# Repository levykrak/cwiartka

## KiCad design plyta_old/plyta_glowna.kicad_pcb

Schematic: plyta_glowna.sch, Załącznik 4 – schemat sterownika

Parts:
C1: 220uF
C2, C6, C7, C8: 100nF
C3, C4: 27pF
C9: 100uF
C10, C11, C12, C13: 10uF
D1: zasilnie
D2, D3, D4, D5, D6, D7, D9, D10, D13, D15: DIODE
FB1: 10uH
IC1: ATMEGA8-MI-sterowanie; MLF32
J2: DB9
J3, J4: RJ45-TRANSFO
K1, K2, K3, K4, K5: PRZEKAZNIK1
P1: +12V
P2: ISP_sterowanie
P4: LCD 2x16
P5: CONN_6
P6: Ledy_kontrolne
Q1, Q2, Q3, Q4, Q5: BC337 lub BC548
R1, R9, R10, R12, R13, R15, R16, R17, R19, R20, R21, R23, R24: 470
R2: 10k
R3: 10
R4, R5, R6, R8: 4,7k
R7: 4,7
R11, R14, R18, R22: 100
RV1: 10k
SW1: Start
SW2: KJS
U1: LM7805
U2, U6: SN75176_lewa
U3, U7: SN75176_prawa
U4: MAX232
U5: LM7805_wyswietlacz
X1: 16MHz

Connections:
1: IC1.9 ((T1)PD5), R8.1
2: IC1.10 ((AIN0)PD6), R7.1
3: IC1.11 ((AIN1)PD7), R6.1
4: IC1.12 ((ICP)PB0), R5.1
5: IC1.13 ((OC1A)PB1), R4.1
+5P: P4.15, U5.VO
+5V: C8.2, C9.1, C12.2, D1.1 (A), FB1.1, IC1.4 (VCC), IC1.6 (VCC), P2.2, P4.2, P6.5, R2.1, R10.2, R12.2, R17.2, R20.2, RV1.1, U1.VO, U2.8 (VCC), U3.8 (VCC), U4.16 (VCC), U6.8 (VCC), U7.8 (VCC)
+12V: D2.1 (A), D3.2 (K), D4.2 (K), D5.2 (K), D6.2 (K), D7.2 (K), J3.1 (TD+), J4.1 (TD+), K1.1, K1.5, K2.1, K2.5, K3.1, K3.5, K4.1, K4.5, K5.1, K5.5, P1.2 (PM)
GND: C1.2, C2.1, C3.2, C4.2, C6.2, C7.2, C8.1, C9.2, C13.1, IC1.3 (GND), IC1.5 (GND), IC1.21 (AGND), J2.5, J3.8, J3.13 (SHIELD), J4.8, J4.13 (SHIELD), P1.1, P2.4, P2.6, P2.8, P2.10, P4.1, P4.5, P4.7, P4.8, P4.9, P4.10, P5.6, Q1.E, Q2.E, Q3.E, Q4.E, Q5.E, R1.2, R3.1, R9.2, R13.2, R16.2, R21.2, RV1.3, SW1.2, SW2.2, U1.GND, U2.2 (RE), U2.3 (DE), U2.4 (DI), U2.5 (GND), U3.2 (RE), U3.3 (DE), U3.4 (DI), U3.5 (GND), U4.15 (GND), U5.GND, U6.2 (RE), U6.3 (DE), U6.4 (DI), U6.5 (GND), U7.2 (RE), U7.3 (DE), U7.4 (DI), U7.5 (GND)
unnamed: J4.3 (TD-), R10.1, R11.2, U2.6 (A)
unnamed: D15.1 (A), R24.2, U3.1 (RO)
unnamed: Q1.B, R4.2
unnamed: D3.1 (A), K1.2, Q1.C
unnamed: IC1.22 (ADC7), SW2.1
unnamed: C11.1, U4.4 (C2+)
unnamed: C11.2, U4.5 (C2-)
unnamed: C10.1, U4.1 (C1+)
unnamed: C10.2, U4.3 (C1-)
unnamed: C12.1, U4.2 (V+)
unnamed: J2.3, U4.13 (R1IN)
unnamed: J2.4, J2.6
unnamed: J2.7, J2.8
unnamed: C13.2, U4.6 (V-)
unnamed: K4.4, P5.2
unnamed: K1.4, P5.5
unnamed: K5.4, P5.1
unnamed: J4.4 (RD+), R9.1, R11.1, U2.7 (B)
unnamed: Q4.B, R7.2
unnamed: D6.1 (A), K4.2, Q4.C
unnamed: K2.4, P5.4
unnamed: Q2.B, R5.2
unnamed: D4.1 (A), K2.2, Q2.C
unnamed: D7.1 (A), K5.2, Q5.C
unnamed: Q5.B, R8.2
unnamed: K3.4, P5.3
unnamed: D5.1 (A), K3.2, Q3.C
unnamed: Q3.B, R6.2
unnamed: IC1.23 ((ADC0)PC0), P4.4
unnamed: IC1.24 ((ADC1)PC1), P4.6
unnamed: IC1.15 ((MOSI/OC2)PB3), P2.1
unnamed: IC1.16 ((MISO)PB4), P2.9
unnamed: IC1.17 ((SCK)PB5), P2.7
unnamed: IC1.19 (ADC6), SW1.1
unnamed: C3.1, IC1.7 (PB6(XTAL1/TOSC1)), X1.1
unnamed: IC1.31 ((TXD)PD1), U4.11 (T1IN)
unnamed: IC1.25 ((ADC2)PC2), P4.11
unnamed: IC1.27 ((ADC4/SDA)PC4), P4.13
unnamed: IC1.30 ((RXD)PD0), U4.12 (R1OUT)
unnamed: P4.3, RV1.2
unnamed: IC1.26 ((ADC3)PC3), P4.12
unnamed: IC1.28 ((ADC5/SCL)PC5), P4.14
unnamed: P4.16, R3.2
unnamed: J2.2, U4.14 (T1OUT)
unnamed: C1.1, C2.2, D2.2 (K), U1.VI, U5.VI
unnamed: C4.1, IC1.8 (PB7(XTAL2/TOSC2)), X1.2
unnamed: C6.1, IC1.20 (AREF)
unnamed: D1.2 (K), R1.1
unnamed: C7.1, FB1.2, IC1.18 (AVCC)
unnamed: IC1.29 (PC6(~RESET~)), P2.5, R2.2
unnamed: J4.5 (RCT), R12.1, R14.1, U3.6 (A)
unnamed: D10.2 (K), D15.2 (K), IC1.1 ((INT1)PD3)
unnamed: J4.6 (RD-), R13.1, R14.2, U3.7 (B)
unnamed: D9.1 (A), R15.2, U6.1 (RO)
unnamed: D9.2 (K), D13.2 (K), IC1.32 ((INT0)PD2)
unnamed: D13.1 (A), R23.2, U2.1 (RO)
unnamed: J3.5 (RCT), R20.1, R22.1, U7.6 (A)
unnamed: J3.4 (RD+), R16.1, R18.1, U6.7 (B)
unnamed: J3.6 (RD-), R21.1, R22.2, U7.7 (B)
unnamed: D10.1 (A), R19.2, U7.1 (RO)
unnamed: J3.3 (TD-), R17.1, R18.2, U6.6 (A)
lewa_meta: P6.3, R15.1
lewa_start: P6.1, R23.1
prawa_meta: P6.4, R19.1
prawa_start: P6.2, R24.1

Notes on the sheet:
ISP
Zasilanie
Wyswietlacz

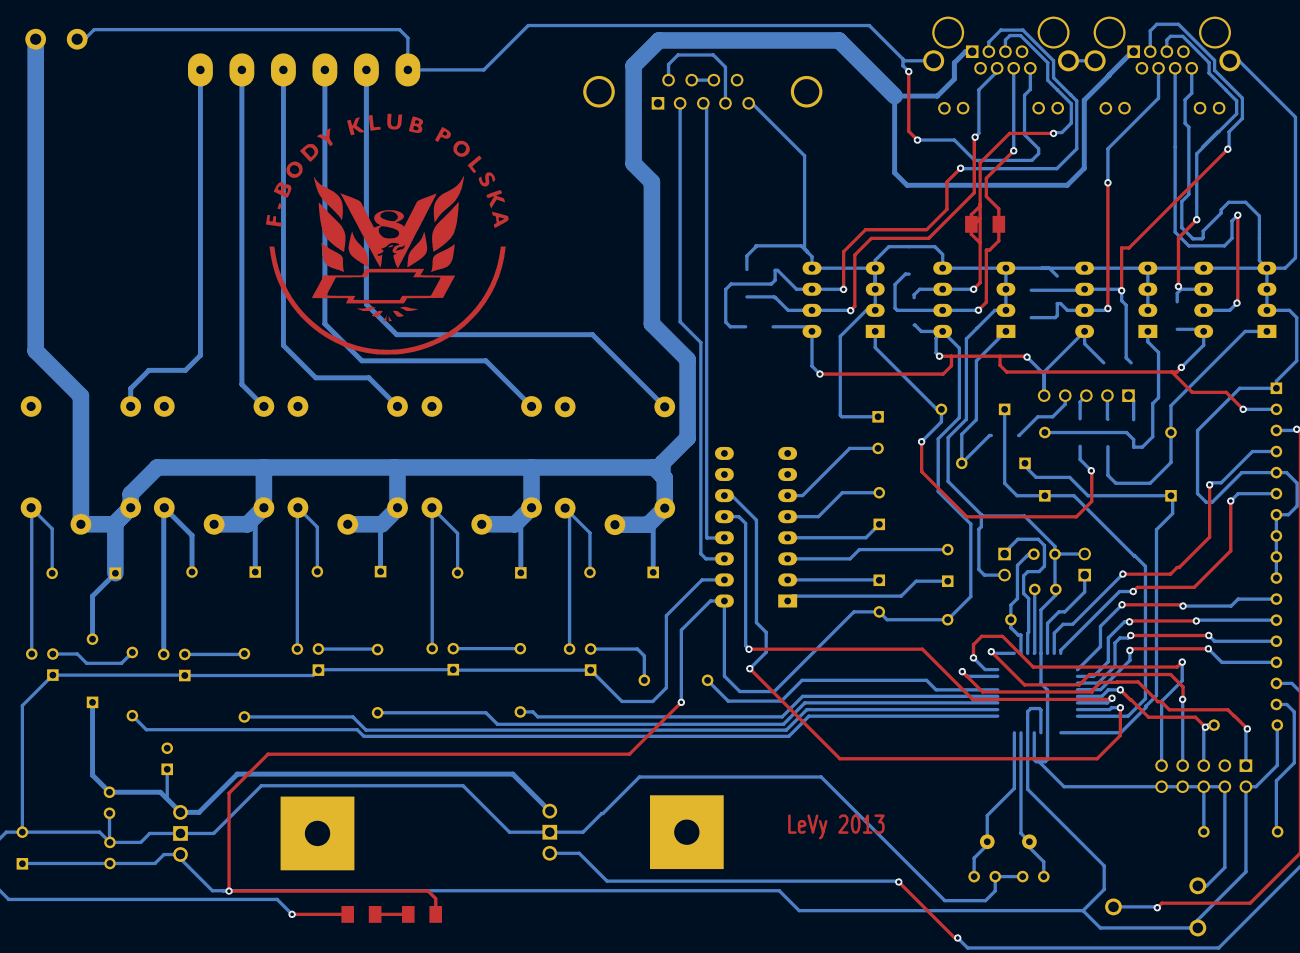
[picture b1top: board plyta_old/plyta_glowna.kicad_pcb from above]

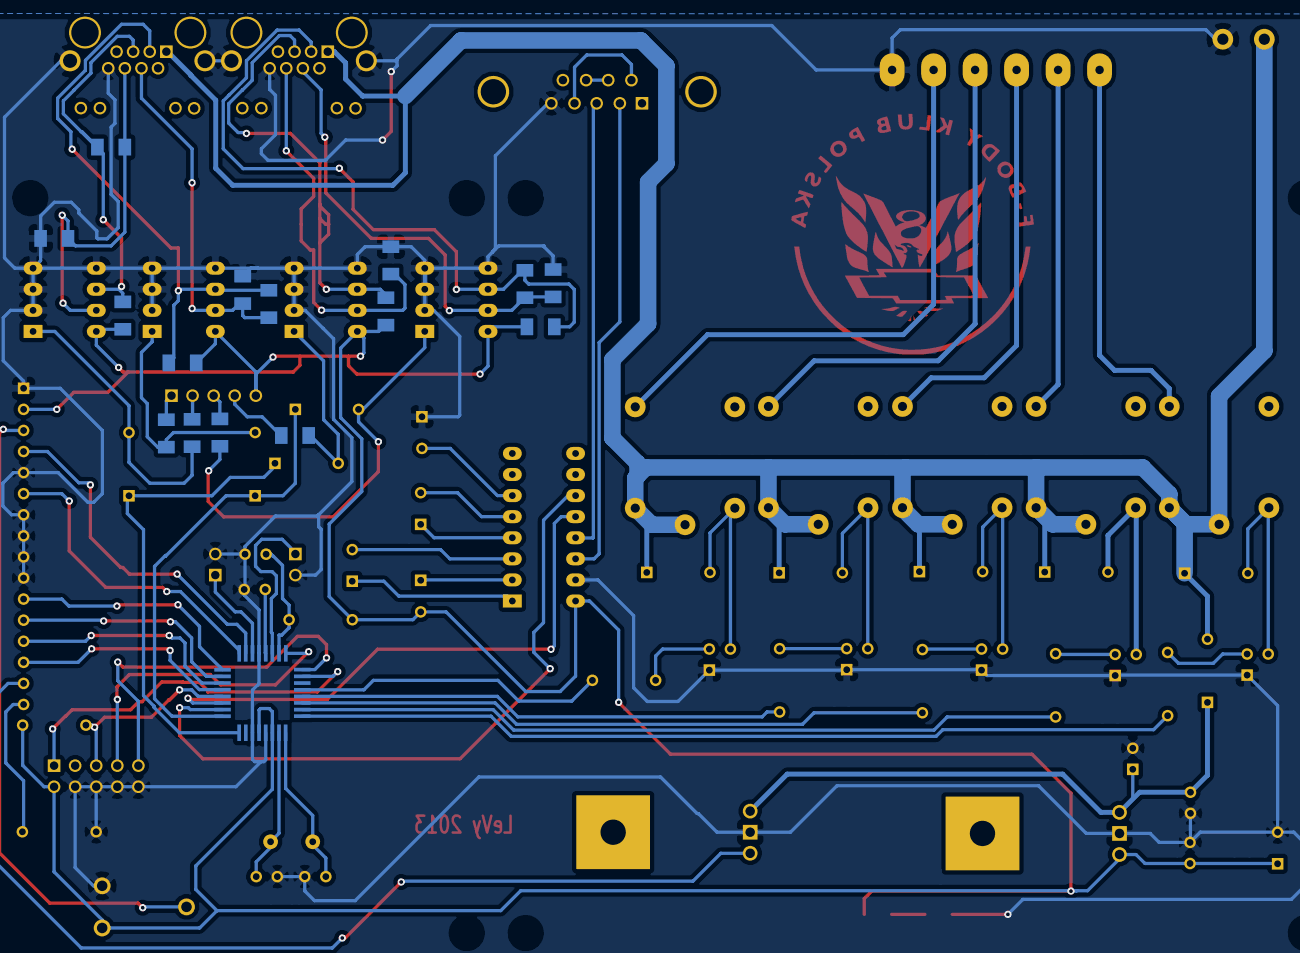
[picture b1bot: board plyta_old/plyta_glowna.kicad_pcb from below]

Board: 2 copper layers, 79 parts (16 on the bottom side), 74 nets.

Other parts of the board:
VAL: logo_fbody_plyta

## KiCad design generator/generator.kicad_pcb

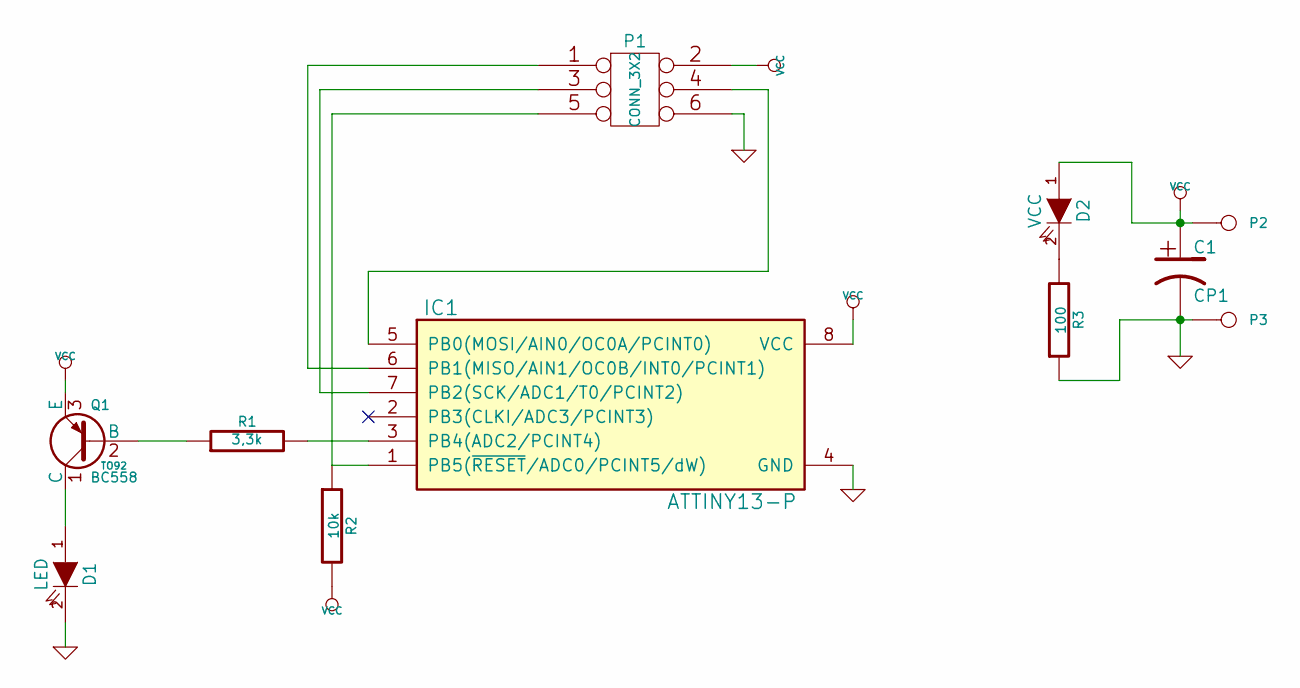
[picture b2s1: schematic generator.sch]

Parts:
C1: CP1
D1: LED
D2: VCC
IC1: ATTINY13-P; DIP8
P1: CONN_3X2
P2, P3: CONN_1
Q1: BC558; TO92
R1: 3,3k
R2: 10k
R3: 100

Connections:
GND: C1.2, D1.2 (K), IC1.4 (GND), P1.6, P3.1, R3.1
unnamed: IC1.1 (PB5(~RESET~/ADC0/PCINT5/dW)), P1.5, R2.1
unnamed: D1.1 (A), Q1.1 (C)
unnamed: IC1.3 (PB4(ADC2/PCINT4)), R1.2
unnamed: Q1.2 (B), R1.1
unnamed: IC1.5 (PB0(MOSI/AIN0/OC0A/PCINT0)), P1.4
unnamed: D2.2 (K), R3.2
unnamed: IC1.7 (PB2(SCK/ADC1/T0/PCINT2)), P1.3
unnamed: IC1.6 (PB1(MISO/AIN1/OC0B/INT0/PCINT1)), P1.1
VCC: C1.1, D2.1 (A), IC1.8 (VCC), P1.2, P2.1, Q1.3 (E), R2.2

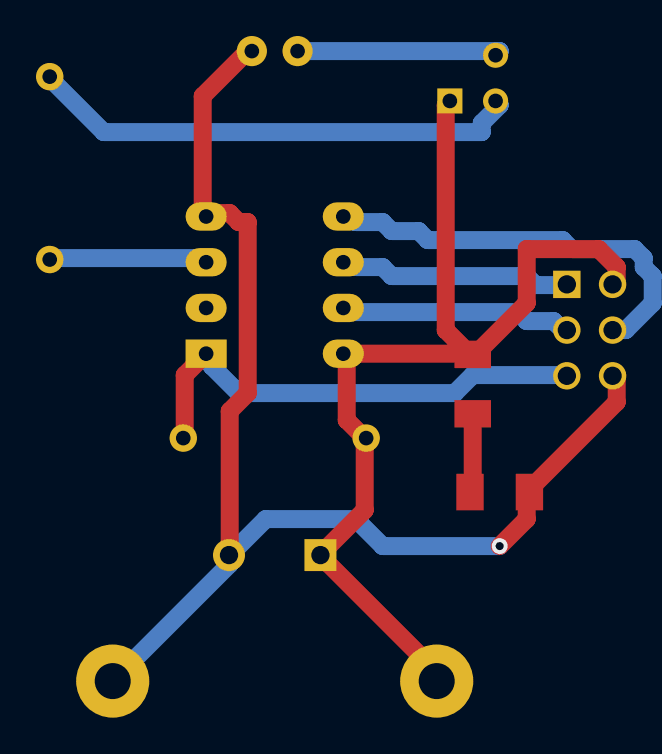
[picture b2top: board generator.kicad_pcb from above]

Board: 2 copper layers, 11 parts (0 on the bottom side), 10 nets.

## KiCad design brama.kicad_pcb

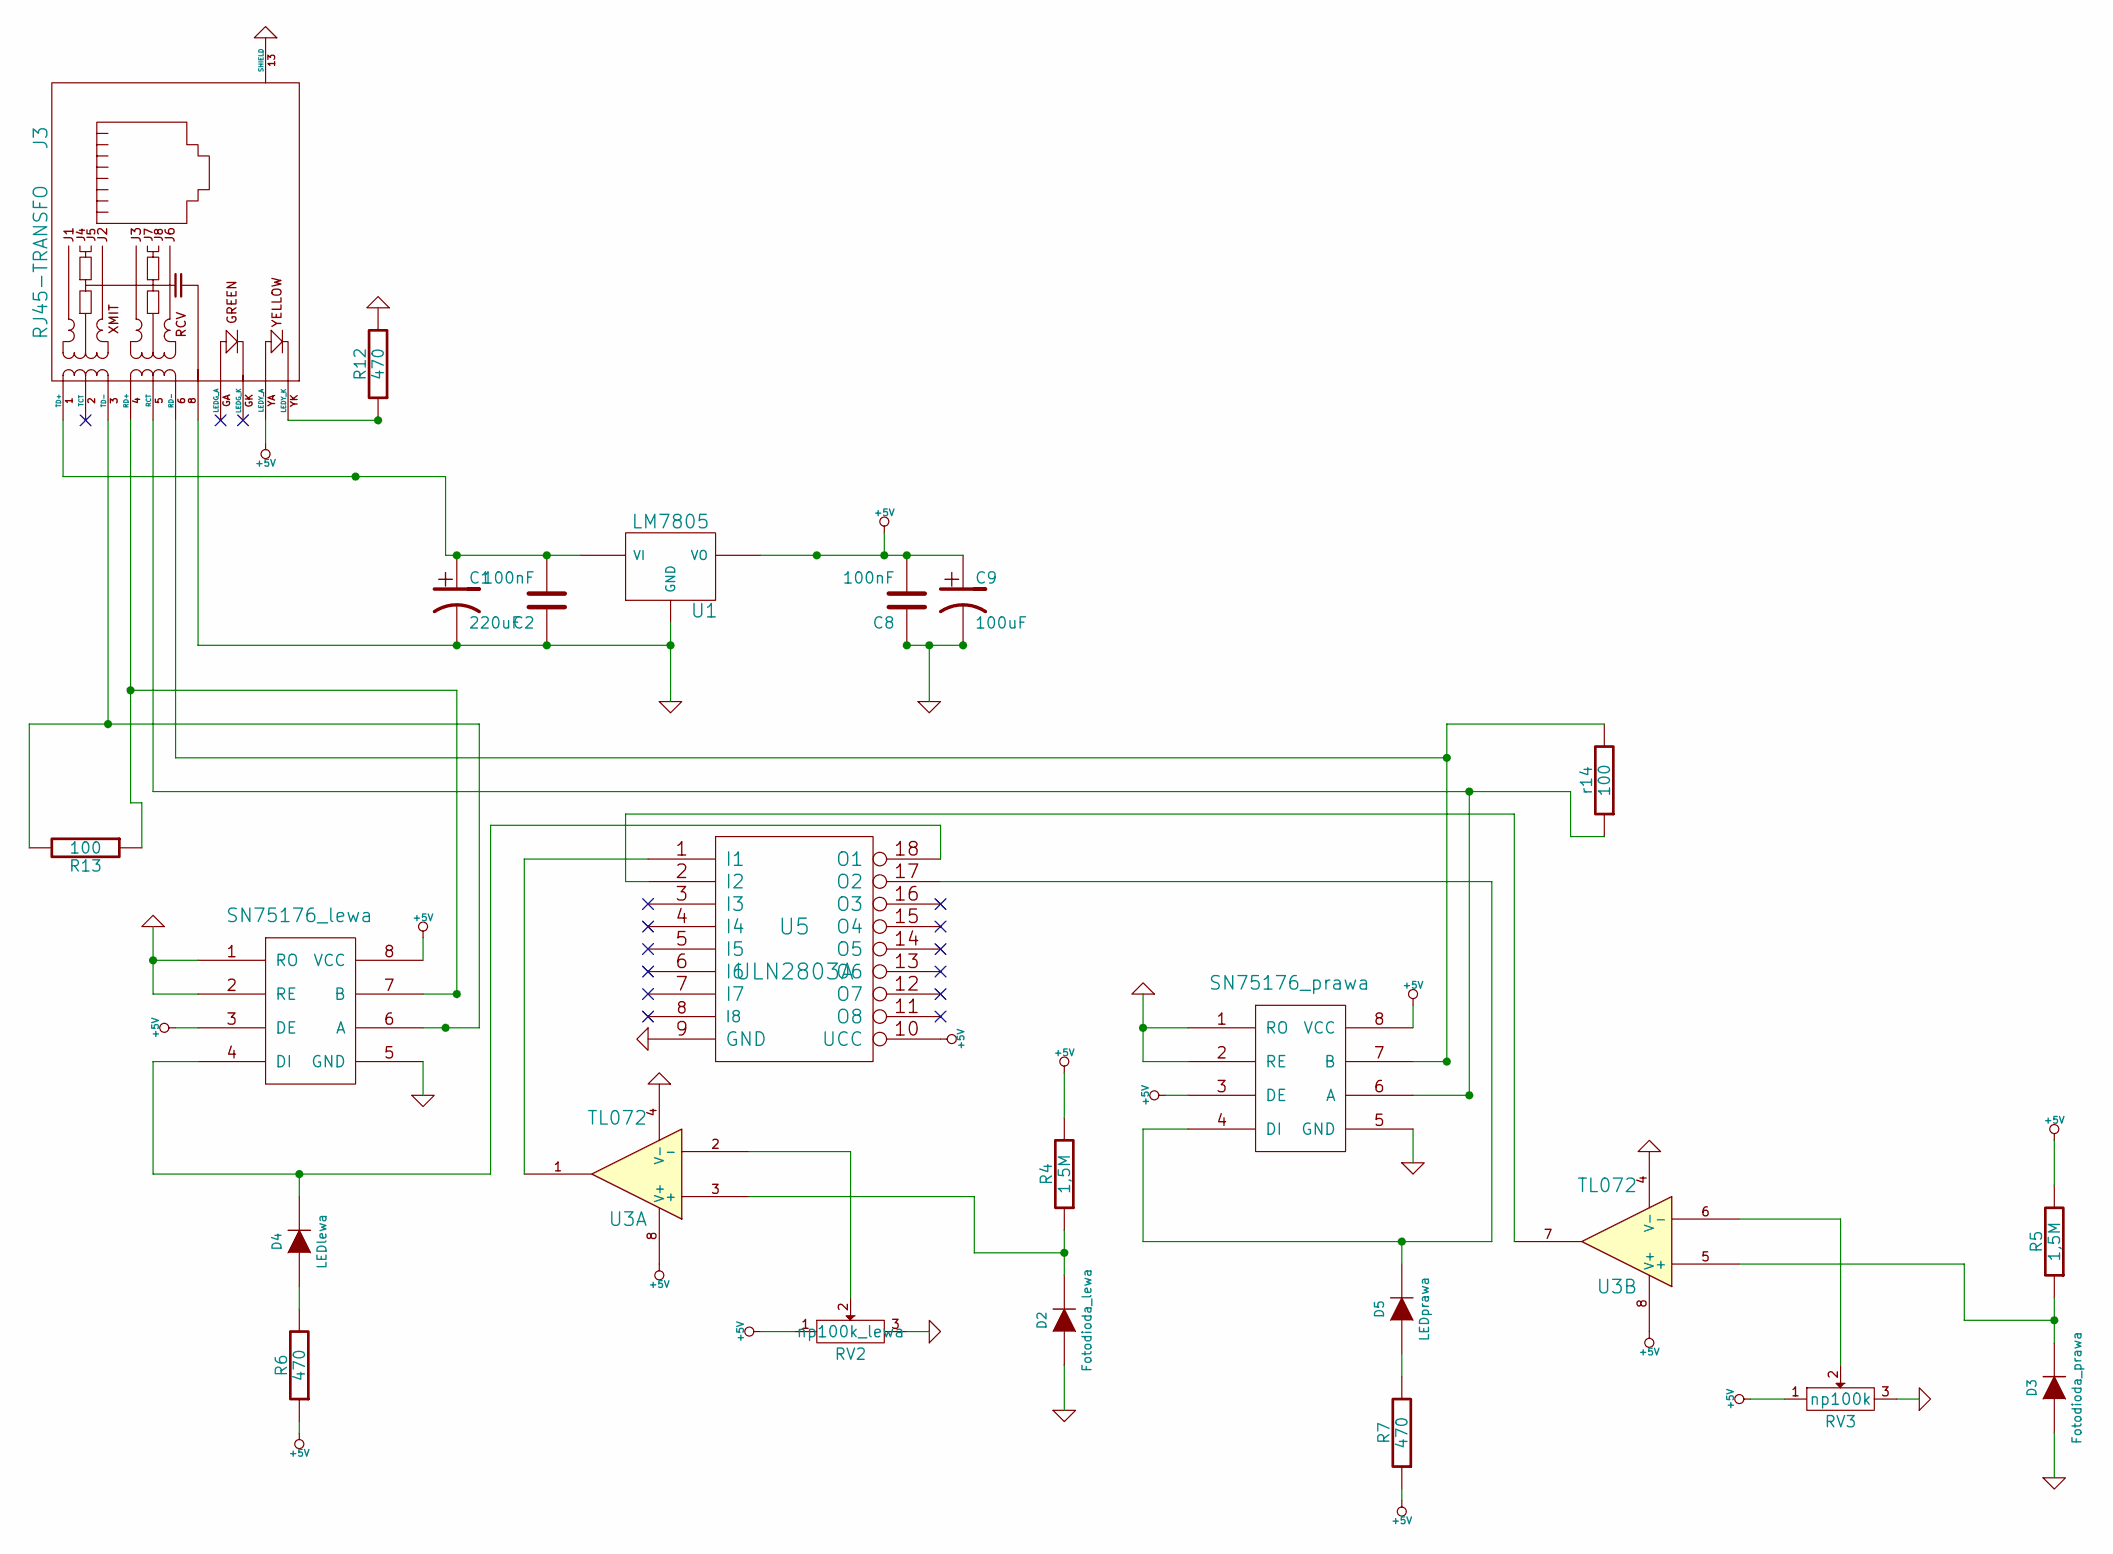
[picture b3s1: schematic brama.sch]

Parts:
C1: 220uF
C2, C8: 100nF
C9: 100uF
D2: Fotodioda_lewa
D3: Fotodioda_prawa
D4: LEDlewa
D5: LEDprawa
J3: RJ45-TRANSFO
R4, R5: 1,5M
R6, R7, R12: 470
R13: 100
RV2: np100k_lewa
RV3: np100k
U1: LM7805
U2: SN75176_lewa
U3: TL072
U4: SN75176_prawa
U5: ULN2803A
r14: 100

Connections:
+5V: C8.2, C9.1, J3.YA (LEDY_A), R4.2, R5.2, R6.1, R7.1, RV2.1, RV3.1, U1.VO, U2.3 (DE), U2.8 (VCC), U3.8 (V+), U4.3 (DE), U4.8 (VCC), U5.10 (UCC)
GND: C1.2, C2.1, C8.1, C9.2, D2.1 (A), D3.1 (A), J3.8, J3.13 (SHIELD), R12.2, RV2.3, RV3.3, U1.GND, U2.1 (RO), U2.2 (RE), U2.5 (GND), U3.4 (V-), U4.1 (RO), U4.2 (RE), U4.5 (GND), U5.9 (GND)
unnamed: RV3.2, U3.6 (-)
unnamed: D4.1 (A), R6.2
unnamed: D5.1 (A), R7.2
unnamed: U3.7, U5.2 (I2)
unnamed: J3.YK (LEDY_K), R12.1
unnamed: U3.1, U5.1 (I1)
unnamed: RV2.2, U3.2 (-)
unnamed: D4.2 (K), U2.4 (DI), U5.18 (O1)
unnamed: D3.2 (K), R5.1, U3.5 (+)
unnamed: J3.4 (RD+), R13.1, U2.7 (B)
unnamed: J3.6 (RD-), U4.7 (B), r14.2
unnamed: D2.2 (K), R4.1, U3.3 (+)
unnamed: C1.1, C2.2, J3.1 (TD+), U1.VI
unnamed: J3.5 (RCT), U4.6 (A), r14.1
unnamed: J3.3 (TD-), R13.2, U2.6 (A)
unnamed: D5.2 (K), U4.4 (DI), U5.17 (O2)

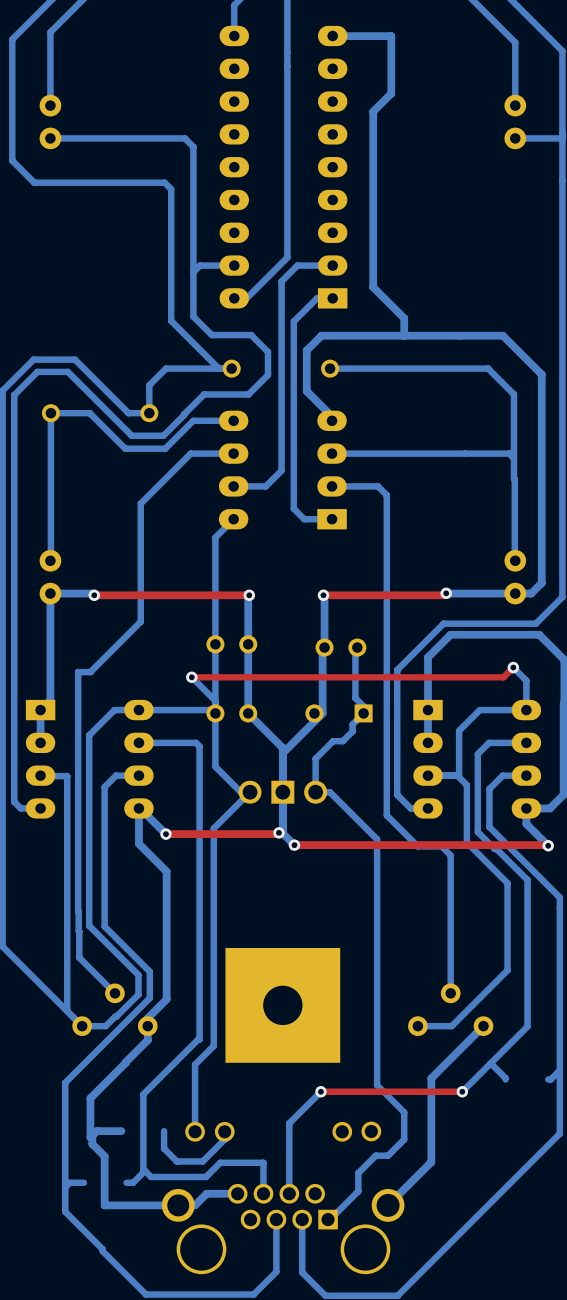
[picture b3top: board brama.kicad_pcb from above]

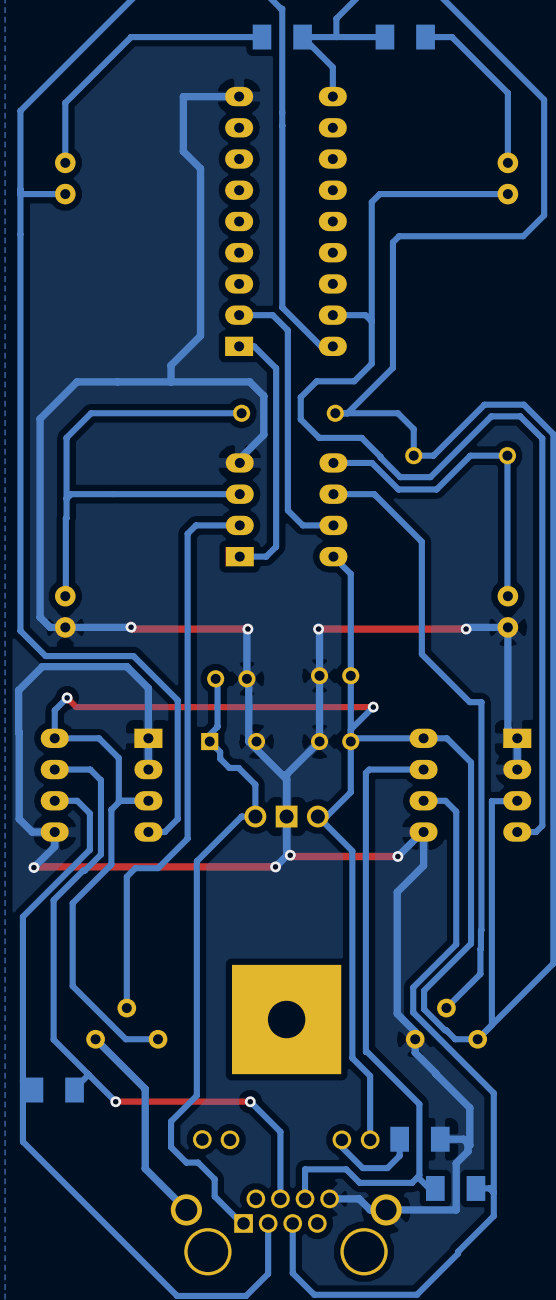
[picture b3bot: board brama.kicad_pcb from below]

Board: 2 copper layers, 23 parts (5 on the bottom side), 18 nets.

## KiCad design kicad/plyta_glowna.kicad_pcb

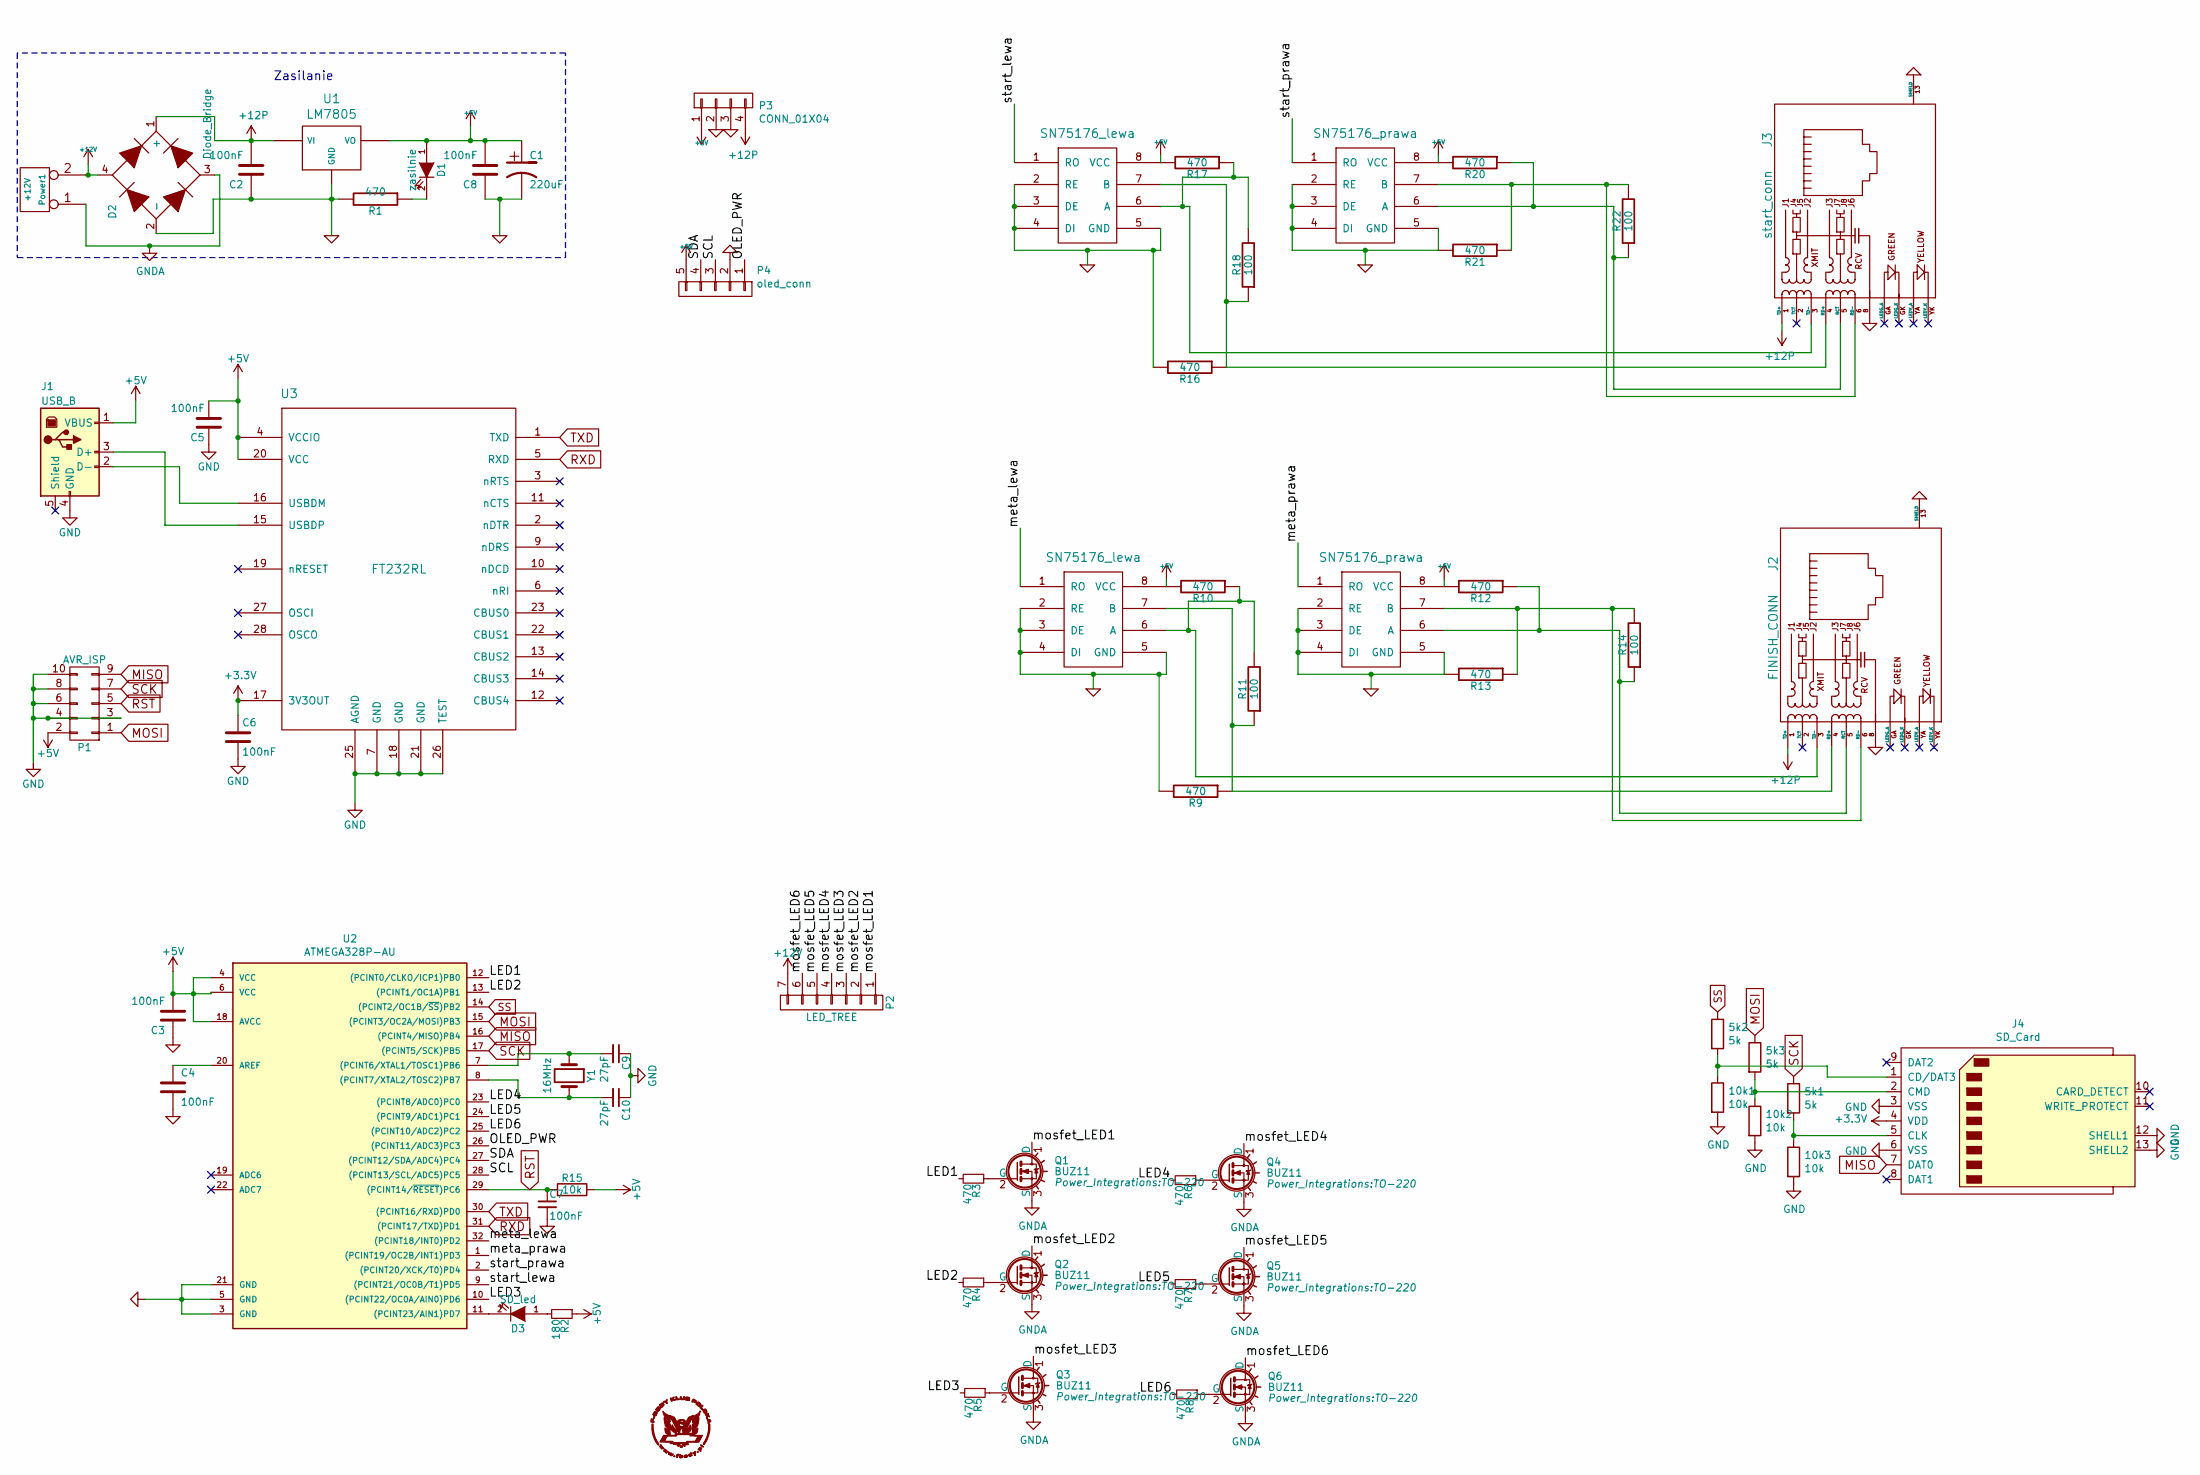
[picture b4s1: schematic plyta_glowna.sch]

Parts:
5k1, 5k2, 5k3: 5k; R_1206
10k1, 10k2, 10k3: 10k; R_1206
C1: 220uF; CP_Elec_10x10.5
C2, C3, C4, C5, C6, C7, C8: 100nF; C_1206
C9, C10: 27pF; C_1206
D1: zasilnie; LED_1206
D2: Diode_Bridge; DB151
D3: SD_led; LED_1206
J1: USB_B
J2: FINISH_CONN; RJHSE538X
J3: start_conn; RJHSE538X
J4: SD_Card; SD_Card_Receptacle
P1: AVR_ISP; Pin_Header_Straight_2x05_Pitch2.54mm
P2: LED_TREE; PhoenixContact_MC-GF_07x5.08mm_Angled_ThreadedFlange
P3: CONN_01X04; Pin_Header_Straight_1x04_Pitch2.54mm
P4: oled_conn; Pin_Header_Straight_1x05_Pitch2.54mm
Power1: +12V; PhoenixContact_MSTBA-G_02x5.08mm_Angled
Q1, Q2, Q3, Q4, Q5, Q6: BUZ11; TO-220
R1, R3, R4, R5, R6, R7, R8, R9, R10, R12, R13, R16, R17, R20, R21: 470; R_1206
R2: 180; R_1206
R11, R14, R18, R22: 100; R_1206
R15: 10k; R_1206
U1: LM7805; TO-252-2_Rectifier
U2: ATMEGA328P-AU; TQFP-32_7x7mm_Pitch0.8mm
U3: FT232RL; SSOP-28_5.3x10.2mm_Pitch0.65mm
U4, U6: SN75176_lewa; SOIC-8-N
U5, U7: SN75176_prawa; SOIC-8-N
Y1: 16MHz; Crystal_SMD_HC49-SD

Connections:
+3V3: C6.1, J4.4 (VDD), U3.17 (3V3OUT)
+5V: C1.1, C3.2, C5.2, C8.2, D1.1 (A), J1.1 (VBUS), P1.2, P3.1, P4.5, R2.1, R10.2, R12.2, R15.1, R17.2, R20.2, U1.3 (VO), U2.4 (VCC), U2.6 (VCC), U2.18 (AVCC), U3.4 (VCCIO), U3.20 (VCC), U4.8 (VCC), U5.8 (VCC), U6.8 (VCC), U7.8 (VCC)
+12P: C2.2, D2.1 (+), J2.1 (TD+), J3.1 (TD+), P3.4, U1.1 (VI)
+12V: D2.4, P2.7, Power1.2 (PM)
/LED1: R3.2, U2.12 ((PCINT0/CLKO/ICP1)PB0)
/LED2: R4.2, U2.13 ((PCINT1/OC1A)PB1)
/LED3: R5.2, U2.10 ((PCINT22/OC0A/AIN0)PD6)
/LED4: R6.2, U2.23 ((PCINT8/ADC0)PC0)
/LED5: R7.2, U2.24 ((PCINT9/ADC1)PC1)
/LED6: R8.2, U2.25 ((PCINT10/ADC2)PC2)
/OLED_PWR: P4.1, U2.26 ((PCINT11/ADC3)PC3); also elsewhere on the board
/SCL: P4.3, U2.28 ((PCINT13/SCL/ADC5)PC5); also elsewhere on the board
/SDA: P4.4, U2.27 ((PCINT12/SDA/ADC4)PC4); also elsewhere on the board
/meta_lewa: U2.32 ((PCINT18/INT0)PD2), U4.1 (RO)
/meta_prawa: U2.1 ((PCINT19/OC2B/INT1)PD3), U5.1 (RO)
/mosfet_LED1: P2.1, Q1.1 (D)
/mosfet_LED2: P2.2, Q2.1 (D)
/mosfet_LED3: P2.3, Q3.1 (D)
/mosfet_LED4: P2.4, Q4.1 (D)
/mosfet_LED5: P2.5, Q5.1 (D)
/mosfet_LED6: P2.6, Q6.1 (D)
/start_lewa: U2.9 ((PCINT21/OC0B/T1)PD5), U6.1 (RO)
/start_prawa: U2.2 ((PCINT20/XCK/T0)PD4), U7.1 (RO)
GND: 10k1.2, 10k2.2, 10k3.2, C1.2, C2.1, C3.1, C4.2, C5.1, C6.2, C7.2, C8.1, C9.1, C10.1, D2.2 (-), J1.4 (GND), J2.8, J2.13 (SHIELD), J3.8, J3.13 (SHIELD), J4.3 (VSS), J4.6 (VSS), J4.12 (SHELL1), J4.13 (SHELL2), P1.3, P1.4, P1.6, P1.8, P1.10, P3.2, P3.3, P4.2, R1.2, R9.2, R13.2, R16.2, R21.2, U1.2 (GND), U2.3 (GND), U2.5 (GND), U2.21 (GND), U3.7 (GND), U3.18 (GND), U3.21 (GND), U3.25 (AGND), U3.26 (TEST), U4.2 (RE), U4.3 (DE), U4.4 (DI), U4.5 (GND), U5.2 (RE), U5.3 (DE), U5.4 (DI), U5.5 (GND), U6.2 (RE), U6.3 (DE), U6.4 (DI), U6.5 (GND), U7.2 (RE), U7.3 (DE), U7.4 (DI), U7.5 (GND); also elsewhere on the board
GNDA: D2.3, Power1.1, Q1.3 (S), Q2.3 (S), Q3.3 (S), Q4.3 (S), Q5.3 (S), Q6.3 (S)
MISO: J4.7 (DAT0), P1.9, U2.16 ((PCINT4/MISO)PB4)
MOSI: 5k3.1, P1.1, U2.15 ((PCINT3/OC2A/MOSI)PB3)
unnamed: 5k2.2, 10k1.1, J4.1 (CD/DAT3)
unnamed: 5k3.2, 10k2.1, J4.2 (CMD)
unnamed: 5k1.2, 10k3.1, J4.5 (CLK)
unnamed: C4.1, U2.20 (AREF)
unnamed: C9.2, U2.7 ((PCINT6/XTAL1/TOSC1)PB6), Y1.1
unnamed: C10.2, U2.8 ((PCINT7/XTAL2/TOSC2)PB7), Y1.2
unnamed: D1.2 (K), R1.1
unnamed: D3.1 (A), R2.2
unnamed: D3.2 (K), U2.11 ((PCINT23/AIN1)PD7)
unnamed: J1.2 (D-), U3.16 (USBDM)
unnamed: J1.3 (D+), U3.15 (USBDP)
unnamed: J2.3 (TD-), R10.1, R11.2, U4.6 (A)
unnamed: J2.4 (RD+), R9.1, R11.1, U4.7 (B)
unnamed: J2.5 (RCT), R12.1, R14.1, U5.6 (A)
unnamed: J2.6 (RD-), R13.1, R14.2, U5.7 (B)
unnamed: J3.3 (TD-), R17.1, R18.2, U6.6 (A)
unnamed: J3.4 (RD+), R16.1, R18.1, U6.7 (B)
unnamed: J3.5 (RCT), R20.1, R22.1, U7.6 (A)
unnamed: J3.6 (RD-), R21.1, R22.2, U7.7 (B)
unnamed: Q1.2 (G), R3.1
unnamed: Q2.2 (G), R4.1
unnamed: Q3.2 (G), R5.1
unnamed: Q4.2 (G), R6.1
unnamed: Q5.2 (G), R7.1
unnamed: Q6.2 (G), R8.1
RST: C7.1, P1.5, R15.2, U2.29 ((PCINT14/~RESET~)PC6)
RXD: U2.31 ((PCINT17/TXD)PD1), U3.5 (RXD)
SCK: 5k1.1, P1.7, U2.17 ((PCINT5/SCK)PB5)
SS: 5k2.1, U2.14 ((PCINT2/OC1B/~SS~)PB2)
TXD: U2.30 ((PCINT16/RXD)PD0), U3.1 (TXD)

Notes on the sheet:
Zasilanie

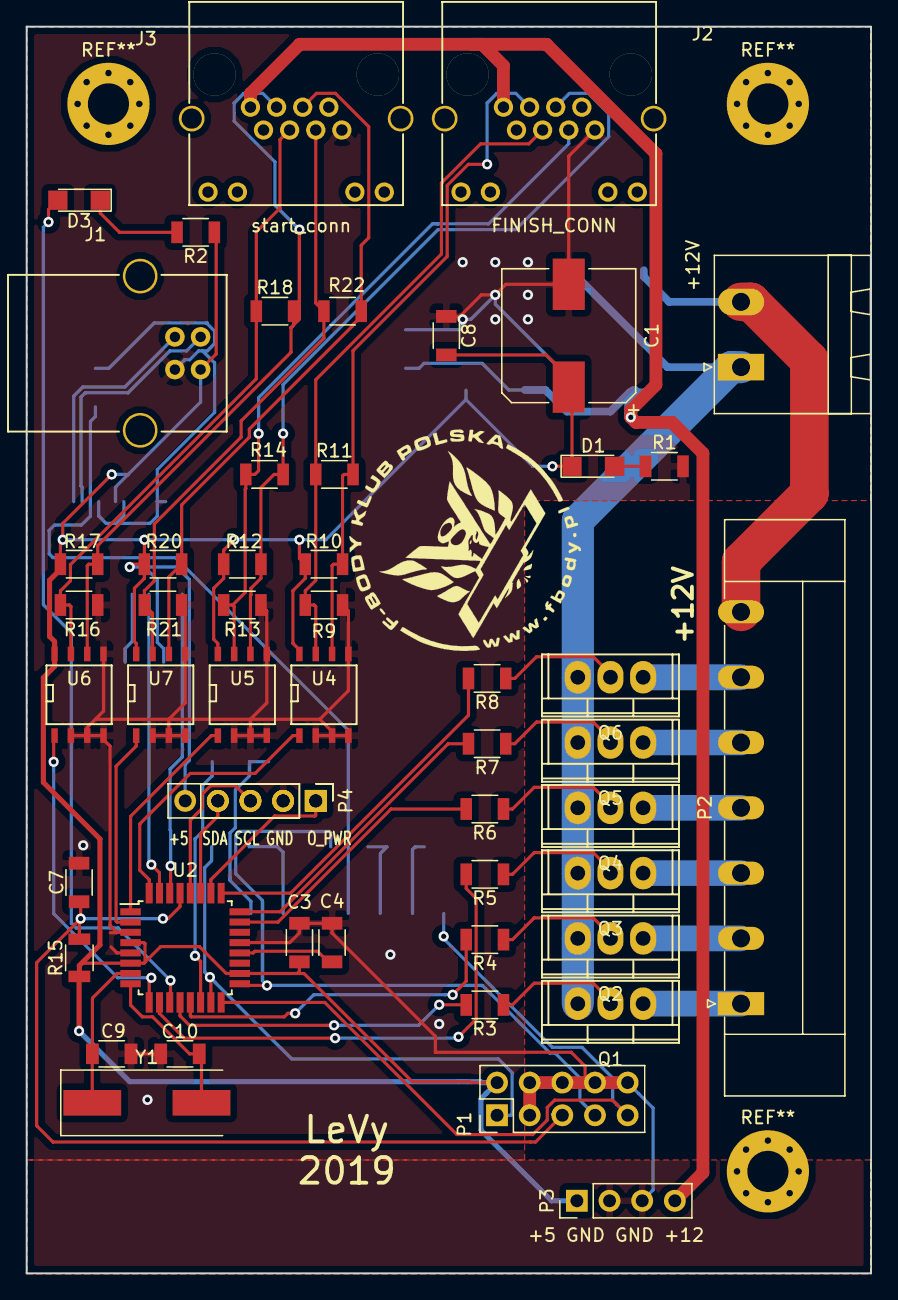
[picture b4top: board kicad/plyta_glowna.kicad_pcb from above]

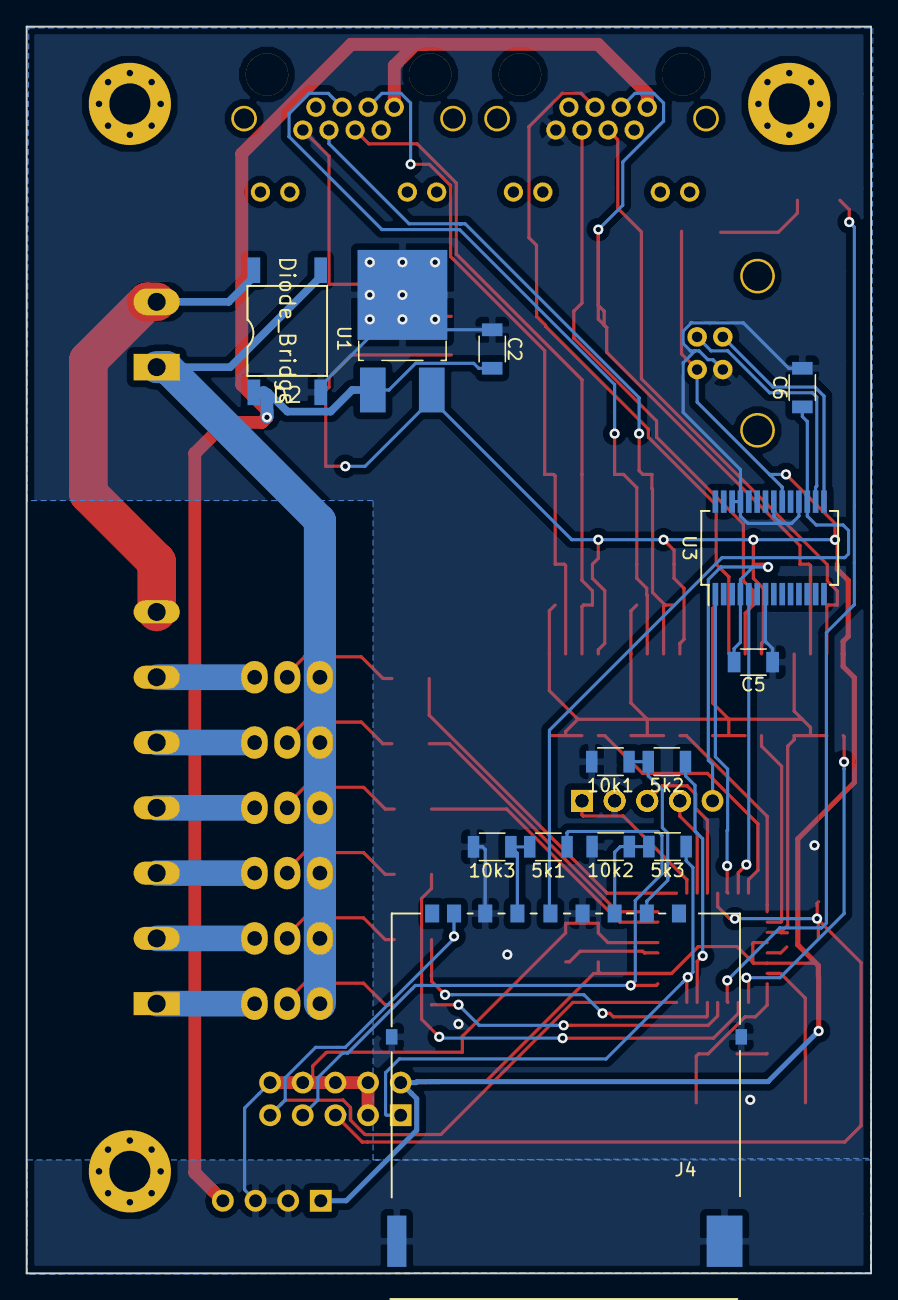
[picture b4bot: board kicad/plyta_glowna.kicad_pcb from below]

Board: 2 copper layers, 65.7 x 97.0 mm, 64 parts (13 on the bottom side), 57 nets.

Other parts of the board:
+5  SDA SCL GND  O_PWR: oled_conn; Pin_Header_Straight_1x04_Pitch2.54mm

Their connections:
/OLED_PWR: +5 SDA SCL GND O_PWR.1; also elsewhere on the board
/SCL: +5 SDA SCL GND O_PWR.3; also elsewhere on the board
/SDA: +5 SDA SCL GND O_PWR.4; also elsewhere on the board
GND: +5 SDA SCL GND O_PWR.2; also elsewhere on the board

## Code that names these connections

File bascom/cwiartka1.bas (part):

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Config Int1 = Rising                                        'meta_prawa
'Config Int0 = Change                                        'meta_lewa
'Config Int1 = Change                                        'meta_prawa
Meta_lewa Alias Pind.2
Meta_prawa Alias Pind.3
Config Pind.5 = Input                                       'pcint21
Start_lewa Alias Pind.5
Config Pind.4 = Input                                       'pcint20
Start_prawa Alias Pind.4

'Set Portd.5                                                 'pullup
'Set Portd.4
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
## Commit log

2019-05-13 pierwszy po zlocie
